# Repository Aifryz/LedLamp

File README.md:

# What is it?
Simply put, it's a controller that drives a PCA9685 12-bit PWM driver.

# How it's made
ATmega16A programmed using modern-ish C++ fetches brightness patterns from program memory, interpolates them and sends them through I2C to two PWM drivers. Each LED can have it's pattern set individualy.

# Why have you made it?
This project started as simple lamp built from 30-50 small white LEDs.
- Then I wanted dimming.
- Then I wanted the circuit to be small.
- Then I wanted multiple patterns that can be displayed.
- Then I wanted to be able to control those patterns.
- Then I decided I will write generalised C++11(or higher) zero-cost-abstractions embedded library to help with the development. 
- Then I threw that idea out. 
- Meanwhile I started thinking about a language designed specifically for a embedded devices, something like a VHDL but more high level that could be translated to given platform C or asm.
That idea shared the fate of the previous one(but I'm still thinking about it).
Then I designed the PCB. After that an idea popped into my head that the lamp could be controlled through serial port from something like ESP8266. IoT anyone?
- The last thing I wanted is to program it using C++ so I could use some of it's nice features like namespaces and templates(used in one place, YAY!).

## Results

Something like 2 years passed from the original idea, some work was done, some was not. But the time has come. 2017 is coming and THAT ONE LITTLE CORNER IN MY HOUSE IS STILL EMPTY AND NOT LIT!
Right now, the lamp hardware is mostly made(90%). The code needs some work. I know I wont be able to finish ALL of my original plans. I just want to make it work and then it can stay in that corner for next two years. Then I could write <strike>a bootloader that would enable me to program the lamp through WiFi</strike> the rest of code needed to realise plans conceived since the work on this project begun.

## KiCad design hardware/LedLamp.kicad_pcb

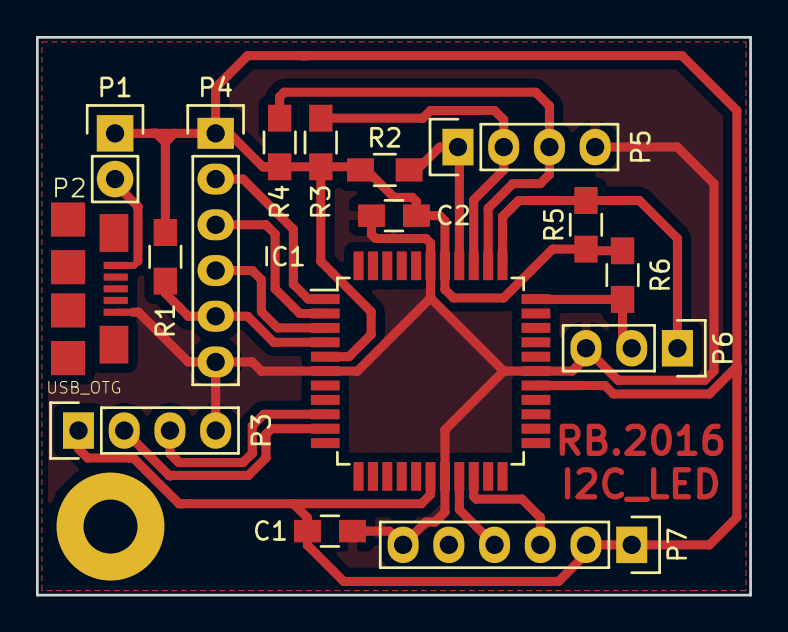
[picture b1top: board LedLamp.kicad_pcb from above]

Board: 2 copper layers, 39.6 x 31.0 mm, 16 parts (0 on the bottom side), 16 nets.

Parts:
C1: 10uF; C_0805_HandSoldering
C2: 220nf; C_0805_HandSoldering
IC1: ATMEGA16-A; LQFP-44_10x10mm_Pitch0.8mm
P1: CONN_01X02; Pin_Header_Straight_1x02
P2: USB_OTG; 10118192-0001LF
P3, P5: CONN_01X04; Pin_Header_Straight_1x04
P4, P7: CONN_01X06; Pin_Header_Straight_1x06
P6: CONN_01X03; Pin_Header_Straight_1x03
R1, R2, R3, R4, R5, R6: 10k; R_0805_HandSoldering

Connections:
GND: C1.2, C2.2, IC1.6, IC1.18, IC1.28, IC1.39, P2.5, P3.4, P4.6, P5.4, P6.3, P7.6
unnamed: IC1.1, P4.2
unnamed: IC1.2, P4.3
unnamed: IC1.3, P4.4
unnamed: IC1.4, P4.5, R1.2
unnamed: IC1.9, P3.3
unnamed: IC1.10, P3.2
unnamed: IC1.19, P7.4
unnamed: IC1.20, P7.3
unnamed: IC1.33, P6.2, R6.2
unnamed: IC1.34, P6.1, R5.2
unnamed: IC1.35, P5.3, R4.2
unnamed: IC1.36, P5.2, R3.2
unnamed: IC1.37, P5.1, R2.2
unnamed: P1.2, P2.1
VCC: C1.1, C2.1, IC1.5, IC1.17, IC1.27, IC1.38, P1.1, P3.1, P4.1, P7.1, P7.2, R1.1, R2.1, R3.1, R4.1, R5.1, R6.1

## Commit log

2016-07-11 Initial
2016-07-15 Added some files, added gitignore and fixed make
2016-08-01 Reinvisioned library, started implementing it
2016-08-02 Saving some changes
2016-08-02 Removed library altogether
2016-08-02 Fixed small bug with uart
2016-08-05 Started adding TWI engine
2016-08-07 Added some rx stuff
2016-08-07 Added volatile specifiers
2016-08-09 Fixed some of the isr
2016-08-09 Fixed over optimization of uart::send code, started fixing TWI engine
2016-08-10 Added stopped callback calling, removed some debugging code
2016-08-10 Somewhere in the isr
2016-08-10 Mostly fixed RXing, now need to clean up code from debugging stuff
2016-08-12 Added PCA header, enums and copied some info from datasheet
2016-08-15 Started adding disableable debugging
2016-08-20 Added way to disable debugging functions in particular modules
2016-08-23 Fixed makefile
2016-08-23 Added basic pseudorandom generator
2016-08-25 Random appears to be working
2016-08-27 Started adding LED control
2016-08-27 Fixed accidentally overriding TWI transactions
2016-09-01 Moved TWI ISR to separate cpp file
2016-09-01 Fixed compilation, started adding features
2016-09-03 Addded working callback
2016-09-04 Redid TwiCallback and added LED_START constant to the PCA9685.hpp file
2016-09-22 Started adding state machine
2016-10-07 Added led state change to state machine
2016-10-07 Removed/disabled some debug messages
2016-10-07 Tired but happy :)
2016-11-15 Fixed bad brightness wraping
2016-12-06 Added hardware files.
2016-12-11 Added some input handling
2016-12-11 Removed some debug code, started adding blinking leds
2016-12-11 Changed the rng to have 32 bit state, added 'alive' and 'dead' states for leds
2016-12-25 First MVP version
